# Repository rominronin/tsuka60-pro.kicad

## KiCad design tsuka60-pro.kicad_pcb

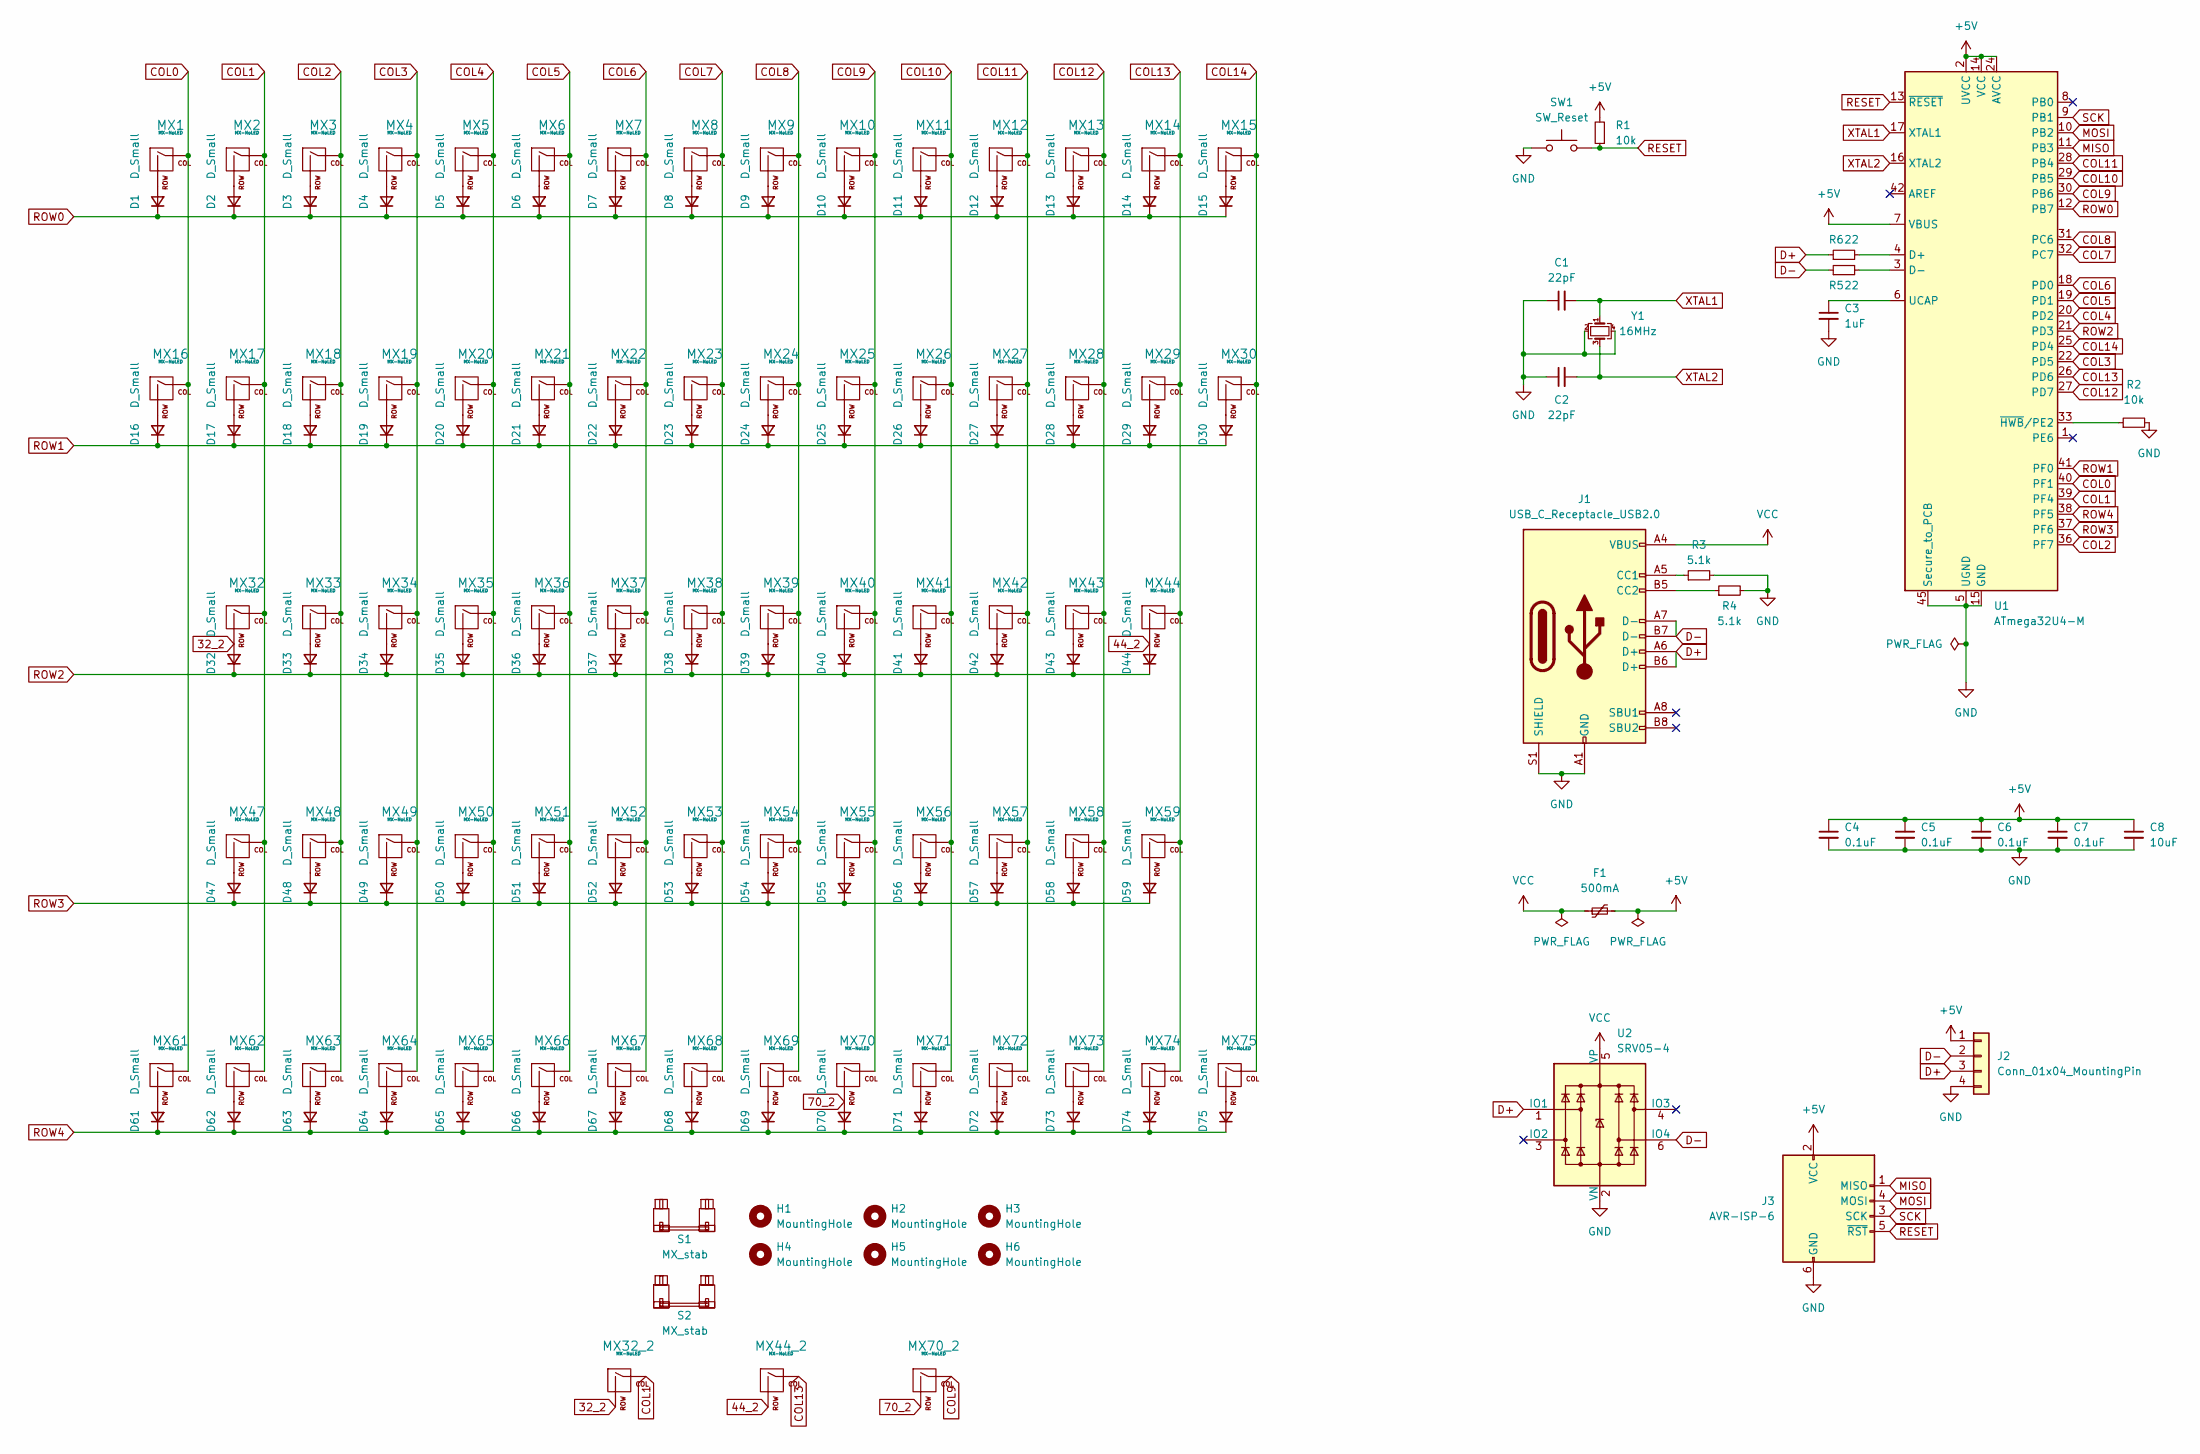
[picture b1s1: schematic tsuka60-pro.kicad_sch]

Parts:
C1, C2: 22pF; C_0603_1608Metric_Pad1.08x0.95mm_HandSolder
C3: 1uF; C_0603_1608Metric_Pad1.08x0.95mm_HandSolder
C4, C5, C6, C7: 0.1uF; C_0603_1608Metric_Pad1.08x0.95mm_HandSolder
C8: 10uF; C_0603_1608Metric_Pad1.08x0.95mm_HandSolder
D1, D2, D3, D4, D5, D6, D7, D8, D9, D10, D11, D12, D13, D14, D15, D16, D17, D18, D19, D20, D21, D22, D23, D24, D25, D26, D27, D28, D29, D30, D32, D33, D34, D35, D36, D37, D38, D39, D40, D41, D42, D43, D44, D47, D48, D49, D50, D51, D52, D53, D54, D55, D56, D57, D58, D59, D61, D62, D63, D64, D65, D66, D67, D68, D69, D70, D71, D72, D73, D74, D75: D_Small; D_SOD-123
F1: 500mA; Fuse_1206_3216Metric_Pad1.42x1.75mm_HandSolder
H1, H2, H3, H4, H5, H6: MountingHole; MountingHole_2.5mm
J1: USB_C_Receptacle_USB2.0; USB_C_Receptacle_HRO_TYPE-C-31-M-12
J2: Conn_01x04_MountingPin; JST_ACH_BM04B-ACHSS-A-GAN-ETF_1x04-1MP_P1.20mm_Vertical
J3: AVR-ISP-6; PinHeader_2x03_P2.54mm_Horizontal
MX1, MX2, MX3, MX4, MX5, MX6, MX7, MX8, MX9, MX10, MX11, MX12, MX13, MX14, MX15, MX16, MX17, MX18, MX19, MX20, MX21, MX22, MX23, MX24, MX25, MX26, MX27, MX28, MX29, MX30, MX33, MX34, MX35, MX36, MX37, MX39, MX40, MX41, MX42, MX43, MX48, MX49, MX50, MX51, MX52, MX53, MX54, MX55, MX56, MX57, MX58, MX61, MX62, MX63, MX64, MX67, MX68, MX69, MX70_2, MX72, MX73, MX74, MX75: MX-NoLED; SW_MX_HS_1u
MX32, MX44: MX-NoLED; SW_MX_HS_1.75u
MX32_2, MX44_2: MX-NoLED; SW_MX_HS_1.75u_stp
MX38, MX47, MX59: MX-NoLED; SW_MX_HS_1.5u
MX65, MX66, MX70, MX71: MX-NoLED; SW_MX_HS_1.25u
R1, R2: 10k; C_0603_1608Metric_Pad1.08x0.95mm_HandSolder
R3, R4: 5.1k; C_0603_1608Metric_Pad1.08x0.95mm_HandSolder
R5, R6: 22; C_0603_1608Metric_Pad1.08x0.95mm_HandSolder
S1: MX_stab; STAB_MX_7u
S2: MX_stab; STAB_MX_2u
SW1: SW_Reset; SW_SPST_SKQG_WithStem
U1: ATmega32U4-M; QFN-44-1EP_7x7mm_P0.5mm_EP5.15x5.15mm
U2: SRV05-4; SOT-23-6
Y1: 16MHz; Crystal_SMD_3225-4Pin_3.2x2.5mm

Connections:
32_2: D32.2 (A), MX32.2 (ROW), MX32_2.2 (ROW)
44_2: D44.2 (A), MX44.2 (ROW), MX44_2.2 (ROW)
70_2: D70.2 (A), MX70.2 (ROW), MX70_2.2 (ROW)
+5V: C4.1, C5.1, C6.1, C7.1, C8.1, F1.2, J2.1, J3.2 (VCC), R1.2, U1.2 (UVCC), U1.7 (VBUS), U1.14 (VCC), U1.24 (AVCC), U1.34 (VCC), U1.44 (AVCC)
COL0: MX1.1 (COL), MX16.1 (COL), MX61.1 (COL), U1.40 (PF1)
COL1: MX2.1 (COL), MX17.1 (COL), MX32.1 (COL), MX32_2.1 (COL), MX47.1 (COL), MX62.1 (COL), U1.39 (PF4)
COL2: MX3.1 (COL), MX18.1 (COL), MX33.1 (COL), MX48.1 (COL), MX63.1 (COL), U1.36 (PF7)
COL3: MX4.1 (COL), MX19.1 (COL), MX34.1 (COL), MX49.1 (COL), MX64.1 (COL), U1.22 (PD5)
COL4: MX5.1 (COL), MX20.1 (COL), MX35.1 (COL), MX50.1 (COL), MX65.1 (COL), U1.20 (PD2)
COL5: MX6.1 (COL), MX21.1 (COL), MX36.1 (COL), MX51.1 (COL), MX66.1 (COL), U1.19 (PD1)
COL6: MX7.1 (COL), MX22.1 (COL), MX37.1 (COL), MX52.1 (COL), MX67.1 (COL), U1.18 (PD0)
COL7: MX8.1 (COL), MX23.1 (COL), MX38.1 (COL), MX53.1 (COL), MX68.1 (COL), U1.32 (PC7)
COL8: MX9.1 (COL), MX24.1 (COL), MX39.1 (COL), MX54.1 (COL), MX69.1 (COL), U1.31 (PC6)
COL9: MX10.1 (COL), MX25.1 (COL), MX40.1 (COL), MX55.1 (COL), MX70.1 (COL), MX70_2.1 (COL), U1.30 (PB6)
COL10: MX11.1 (COL), MX26.1 (COL), MX41.1 (COL), MX56.1 (COL), MX71.1 (COL), U1.29 (PB5)
COL11: MX12.1 (COL), MX27.1 (COL), MX42.1 (COL), MX57.1 (COL), MX72.1 (COL), U1.28 (PB4)
COL12: MX13.1 (COL), MX28.1 (COL), MX43.1 (COL), MX58.1 (COL), MX73.1 (COL), U1.27 (PD7)
COL13: MX14.1 (COL), MX29.1 (COL), MX44.1 (COL), MX44_2.1 (COL), MX59.1 (COL), MX74.1 (COL), U1.26 (PD6)
COL14: MX15.1 (COL), MX30.1 (COL), MX75.1 (COL), U1.25 (PD4)
D+: J1.A6 (D+), J1.B6 (D+), J2.3, R6.1, U2.1 (IO1)
D-: J1.A7 (D-), J1.B7 (D-), J2.2, R5.1, U2.6 (IO4)
GND: C1.1, C2.1, C3.2, C4.2, C5.2, C6.2, C7.2, C8.2, J1.A1 (GND), J1.A12 (GND), J1.B1 (GND), J1.B12 (GND), J1.S1 (SHIELD), J2.4, J3.6 (GND), R2.2, R3.2, R4.2, SW1.1, U1.5 (UGND), U1.15 (GND), U1.23 (GND), U1.35 (GND), U1.43 (GND), U1.45 (Secure_to_PCB), U2.2 (VN), Y1.2, Y1.4
MISO: J3.1 (MISO), U1.11 (PB3)
MOSI: J3.4 (MOSI), U1.10 (PB2)
unnamed: D1.2 (A), MX1.2 (ROW)
unnamed: D2.2 (A), MX2.2 (ROW)
unnamed: D3.2 (A), MX3.2 (ROW)
unnamed: D4.2 (A), MX4.2 (ROW)
unnamed: D5.2 (A), MX5.2 (ROW)
unnamed: D6.2 (A), MX6.2 (ROW)
unnamed: D7.2 (A), MX7.2 (ROW)
unnamed: D8.2 (A), MX8.2 (ROW)
unnamed: D9.2 (A), MX9.2 (ROW)
unnamed: D10.2 (A), MX10.2 (ROW)
unnamed: D11.2 (A), MX11.2 (ROW)
unnamed: D12.2 (A), MX12.2 (ROW)
unnamed: D13.2 (A), MX13.2 (ROW)
unnamed: D14.2 (A), MX14.2 (ROW)
unnamed: D15.2 (A), MX15.2 (ROW)
unnamed: D16.2 (A), MX16.2 (ROW)
unnamed: D17.2 (A), MX17.2 (ROW)
unnamed: D18.2 (A), MX18.2 (ROW)
unnamed: D19.2 (A), MX19.2 (ROW)
unnamed: D20.2 (A), MX20.2 (ROW)
unnamed: D21.2 (A), MX21.2 (ROW)
unnamed: D22.2 (A), MX22.2 (ROW)
unnamed: D23.2 (A), MX23.2 (ROW)
unnamed: D24.2 (A), MX24.2 (ROW)
unnamed: D25.2 (A), MX25.2 (ROW)
unnamed: D26.2 (A), MX26.2 (ROW)
unnamed: D27.2 (A), MX27.2 (ROW)
unnamed: D28.2 (A), MX28.2 (ROW)
unnamed: D29.2 (A), MX29.2 (ROW)
unnamed: D30.2 (A), MX30.2 (ROW)
unnamed: D33.2 (A), MX33.2 (ROW)
unnamed: D34.2 (A), MX34.2 (ROW)
unnamed: D35.2 (A), MX35.2 (ROW)
unnamed: D36.2 (A), MX36.2 (ROW)
unnamed: D37.2 (A), MX37.2 (ROW)
unnamed: D38.2 (A), MX38.2 (ROW)
unnamed: D39.2 (A), MX39.2 (ROW)
unnamed: D40.2 (A), MX40.2 (ROW)
unnamed: D41.2 (A), MX41.2 (ROW)
unnamed: D42.2 (A), MX42.2 (ROW)
unnamed: D43.2 (A), MX43.2 (ROW)
unnamed: D47.2 (A), MX47.2 (ROW)
unnamed: D48.2 (A), MX48.2 (ROW)
unnamed: D49.2 (A), MX49.2 (ROW)
unnamed: D50.2 (A), MX50.2 (ROW)
unnamed: D51.2 (A), MX51.2 (ROW)
unnamed: D52.2 (A), MX52.2 (ROW)
unnamed: D53.2 (A), MX53.2 (ROW)
unnamed: D54.2 (A), MX54.2 (ROW)
unnamed: D55.2 (A), MX55.2 (ROW)
unnamed: D56.2 (A), MX56.2 (ROW)
unnamed: D57.2 (A), MX57.2 (ROW)
unnamed: D58.2 (A), MX58.2 (ROW)
unnamed: D59.2 (A), MX59.2 (ROW)
unnamed: D61.2 (A), MX61.2 (ROW)
unnamed: D62.2 (A), MX62.2 (ROW)
unnamed: D63.2 (A), MX63.2 (ROW)
unnamed: D64.2 (A), MX64.2 (ROW)
unnamed: D65.2 (A), MX65.2 (ROW)
unnamed: D66.2 (A), MX66.2 (ROW)
unnamed: D67.2 (A), MX67.2 (ROW)
unnamed: D68.2 (A), MX68.2 (ROW)
unnamed: D69.2 (A), MX69.2 (ROW)
unnamed: D71.2 (A), MX71.2 (ROW)
unnamed: D72.2 (A), MX72.2 (ROW)
unnamed: D73.2 (A), MX73.2 (ROW)
unnamed: D74.2 (A), MX74.2 (ROW)
unnamed: D75.2 (A), MX75.2 (ROW)
unnamed: J1.A5 (CC1), R3.1
unnamed: J1.B5 (CC2), R4.1
unnamed: R6.2, U1.4 (D+)
unnamed: R5.2, U1.3 (D-)
unnamed: C3.1, U1.6 (UCAP)
unnamed: R2.1, U1.33 (~HWB/PE2)
RESET: J3.5 (~RST), R1.1, SW1.2, U1.13 (~RESET)
ROW0: D1.1 (K), D2.1 (K), D3.1 (K), D4.1 (K), D5.1 (K), D6.1 (K), D7.1 (K), D8.1 (K), D9.1 (K), D10.1 (K), D11.1 (K), D12.1 (K), D13.1 (K), D14.1 (K), D15.1 (K), U1.12 (PB7)
ROW1: D16.1 (K), D17.1 (K), D18.1 (K), D19.1 (K), D20.1 (K), D21.1 (K), D22.1 (K), D23.1 (K), D24.1 (K), D25.1 (K), D26.1 (K), D27.1 (K), D28.1 (K), D29.1 (K), D30.1 (K), U1.41 (PF0)
ROW2: D32.1 (K), D33.1 (K), D34.1 (K), D35.1 (K), D36.1 (K), D37.1 (K), D38.1 (K), D39.1 (K), D40.1 (K), D41.1 (K), D42.1 (K), D43.1 (K), D44.1 (K), U1.21 (PD3)
ROW3: D47.1 (K), D48.1 (K), D49.1 (K), D50.1 (K), D51.1 (K), D52.1 (K), D53.1 (K), D54.1 (K), D55.1 (K), D56.1 (K), D57.1 (K), D58.1 (K), D59.1 (K), U1.37 (PF6)
ROW4: D61.1 (K), D62.1 (K), D63.1 (K), D64.1 (K), D65.1 (K), D66.1 (K), D67.1 (K), D68.1 (K), D69.1 (K), D70.1 (K), D71.1 (K), D72.1 (K), D73.1 (K), D74.1 (K), D75.1 (K), U1.38 (PF5)
SCK: J3.3 (SCK), U1.9 (PB1)
VCC: F1.1, J1.A4 (VBUS), J1.A9 (VBUS), J1.B4 (VBUS), J1.B9 (VBUS), U2.5 (VP)
XTAL1: C1.2, U1.17 (XTAL1), Y1.1
XTAL2: C2.2, U1.16 (XTAL2), Y1.3

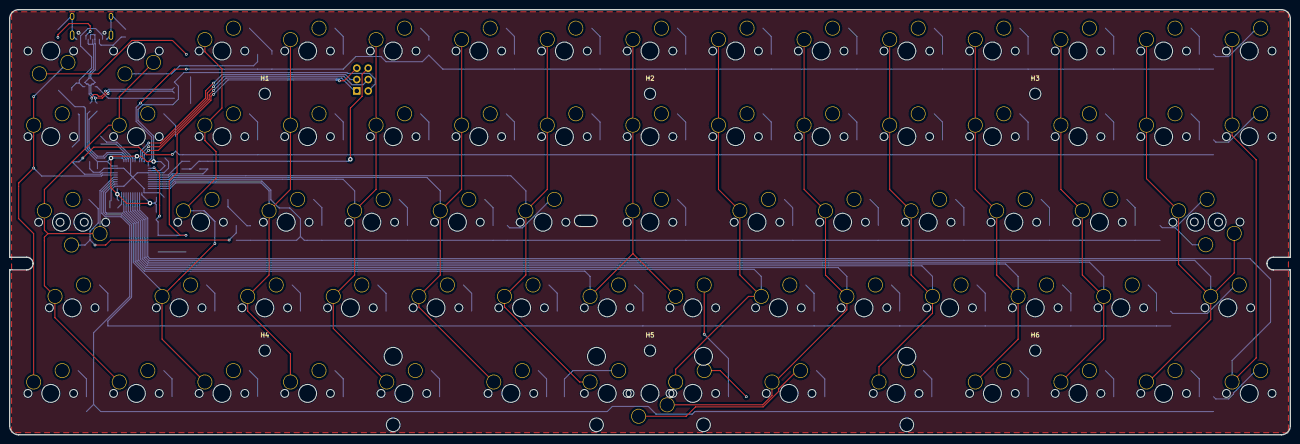
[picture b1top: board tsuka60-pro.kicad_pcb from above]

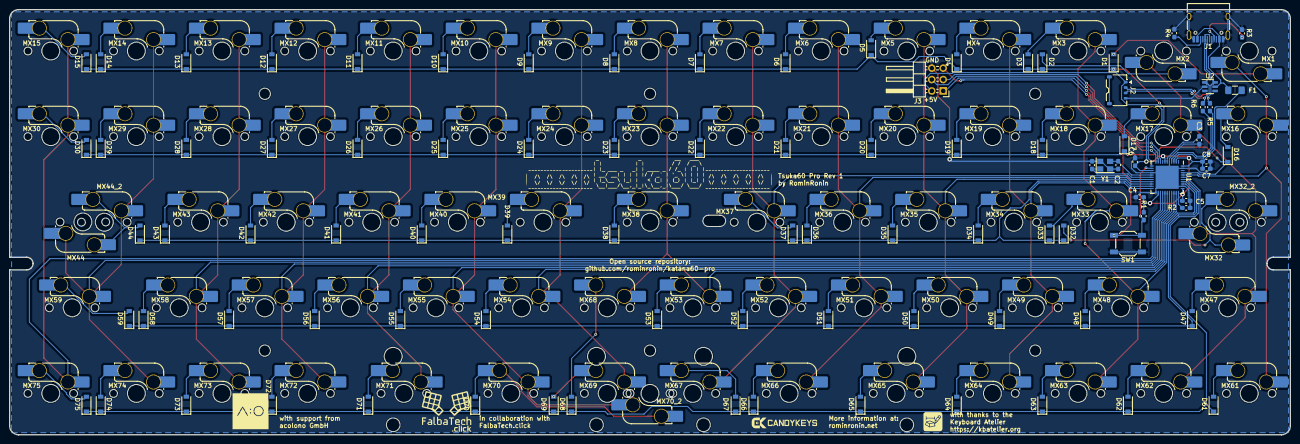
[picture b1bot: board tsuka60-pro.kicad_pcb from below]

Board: 2 copper layers, 285.0 x 94.6 mm, 175 parts (167 on the bottom side), 108 nets.

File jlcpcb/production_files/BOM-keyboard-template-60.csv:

Comment,Designator,Footprint,LCSC
ATmega32U4-M,U1,QFN-44-1EP_7x7mm_P0.5mm_EP5.15x5.15mm,C112161
16MHz,Y1,Crystal_SMD_3225-4Pin_3.2x2.5mm,C13738
0.1uF,"C4,C5,C6,C7",C_0603_1608Metric_Pad1.08x0.95mm_HandSolder,C14663
1uF,C3,C_0603_1608Metric_Pad1.08x0.95mm_HandSolder,C15849
22pF,"C1,C2",C_0603_1608Metric_Pad1.08x0.95mm_HandSolder,C1653
10uF,C8,C_0603_1608Metric_Pad1.08x0.95mm_HandSolder,C19702
USB_C_Receptacle_USB2.0,J1,USB_C_Receptacle_HRO_TYPE-C-31-M-14,C223907
5k,"R3,R4",C_0603_1608Metric_Pad1.08x0.95mm_HandSolder,C22809
10k,"R1,R2",C_0603_1608Metric_Pad1.08x0.95mm_HandSolder,C25804
SW_Reset,SW1,SW_SPST_SKQG_WithStem,C318884
22,"R5,R6",C_0603_1608Metric_Pad1.08x0.95mm_HandSolder,C4190
MX-NoLED,"MX1-22,MX24-37,MX37_2,MX39,MX39_2,MX40-65,MX67-69,MX71-75",SW_MX_HS_1u,C5156480
Conn_01x04_MountingPin,J2,JST_ACH_BM04B-ACHSS-A-GAN-ETF_1x04-1MP_P1.20mm_Vertical,C528030
500mA,F1,Fuse_1206_3216Metric_Pad1.42x1.75mm_HandSolder,C69688
SRV05-4,U2,SOT-23-6,C85364
D_Small,"D1-22,D24-37,D39-65,D67-69,D71-75",D_SOD-123,C8598

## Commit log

2023-05-20 Transferring updates from the Katana60 Pro
2023-05-21 Update the schematic, footprints and layout
2023-05-22 Parts placement.
2023-05-23 Further update traces
2023-05-23 Finish traces, draft 1
2023-05-24 Update traces
2023-12-27 Made important changes to the keyboard, re-exported production files
2024-01-14 Add missing trace
2024-01-21 Repair BOM, update USB-C component, footprint and placement
2024-01-21 Update some traces
2024-01-21 Add mounting holes and re-export productions files
2024-01-23 Updated BOM and production files
2024-01-25 SIP socket placement
2024-01-26 Relocate ISP header, retrace
2024-01-26 Add 2u stab, relocate mounting holes
2024-02-04 Reposition and retrace ISP footprint, update BOM and production files
2024-03-05 Final changes before getting a second pair of eyes
2025-09-04 Fixed shorting traces
2026-01-11 Adjust some silkscreens and update DRC exclusions
2026-01-12 Fix DRC errors
2026-01-12 Falbatech logo silkscreen
2026-01-12 installed JLCPCB tools, which updated BOM libraries
2026-01-18 Update traces and BOM, production files
2026-01-22 Fixed some ERC and DRC errors
2026-01-23 update silkscreen
